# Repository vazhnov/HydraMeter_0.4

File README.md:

# HydraMeter_0.4

Open source [multimeter](https://en.wikipedia.org/wiki/Multimeter)

## Intro

I don't have detailed assembly documents yet, and this isn't really well made for easy assembly in any case, it's a proof of concept at the moment.

There are some more details here: https://hackaday.io/project/176607-hydrameter but it's not much. Mainly a few entries down there's a tour
of how the analog stuff works: https://hackaday.io/project/176607-hydrameter/log/223270-schematic-and-operation

## Repository structure

* Directory [MMTR_AFE_00_04_TORELEASE](./MMTR_AFE_00_04_TORELEASE) contains all schematics and board layouts.
* Directory [MMTR_V00_03_Case](./MMTR_V00_03_Case) contains all the CAD, source type is solidedge (they have a free community edition).
* Directory [Code -> HackBoard_V02_10_shbrd_cal](./Code/HackBoard_V02_10_shbrd_cal/) contains the code for the analog frontend.
* Directory [Code -> Display_VP_10_WirelessV2_SC](./Code/Display_VP_10_WirelessV2_SC/) contains code for the display section.

## Notes

I would recommend 24 to 28 AWG stranded wire for connecting to switches, except the mA/uA switch, for which I'd use 20AWG.
The switches should pull inputs to the 74165s to ground, for numbering you'll have to check the code (or adjust it), when assembled I just
wired up all of them then recorded which switch went where, I don't have a list or diagram. On the board these are labeled A-H, one set
is near the middle of the board, the other next to the module connector.

Hardwired connections are: the two ohms jumpers (J7 and J8) are wired to the second pole of the lower-right switch (right from the front),
and the mA/uA switch goes to J5 and J6.

There's a hardwired connection from J30 to J34, which should be made with at least 18AWG wire, as it carries the full current for the 10A range.

## Tweaks

Note that this version of the PCB has some tweaks from the last manufactured version,
these have not been verified to work.

The as-made PCB is under version 0.3,
however, this version requires significant manual rework including:
* pullup resistors for all switches to D3V3
* cutting jumpers to the Module outputs (J96-99, to configure them as inputs), and wiring switches to them
* additional capacitors on D3V3 to D0V, to stabilize the rail when using a radio module
* DNP U5, and bridge pin 3 to pin 4
* DNP: R74, D5, C72, R76, R77, U26, R78, Q20, Q21, R80, R79
* Replace R33 with a ~16K resistor, or two 33K in parallel
* Manually cut the trace going to pin 10 on U12, U13 and U16 (pulling it to D0V), and wire that pin on the chip to D3V3
* U18 has the wrong footprint (SOIC-16 used on the board, the actual chip is a SOIC-14).
* Angle U18 such that only pins 14-9 make contact with the board (so pins 1-7 are above the surface), and solder in place.
* Then manually wire pins 2-7 to the appropriate pads with short wires.
* If using a battery, a protected cell must be used, there is no circuitry onboard to protect from over or under voltage.
* Positive should be soldered to J10, negative to J11.

To charge, two diodes can be placed in series from VBUS on the
PI pico (MCU_VBUS) to battery positive (charging the battery when USB is plugged in). Bypassing one of the diodes with
a 50 or 100 ohm resistor can improve charge time. This however WILL overcharge the battery if proper cell protection
is not in place! This is a terrible hack solution I used to get something working in like an hour. Use a charger IC
or board or something.

## License

This project uses the CERN Open Hardware Licence Version 2 - Strongly Reciprocal.
Any derived works must fall under the same license and must be open source themselves.

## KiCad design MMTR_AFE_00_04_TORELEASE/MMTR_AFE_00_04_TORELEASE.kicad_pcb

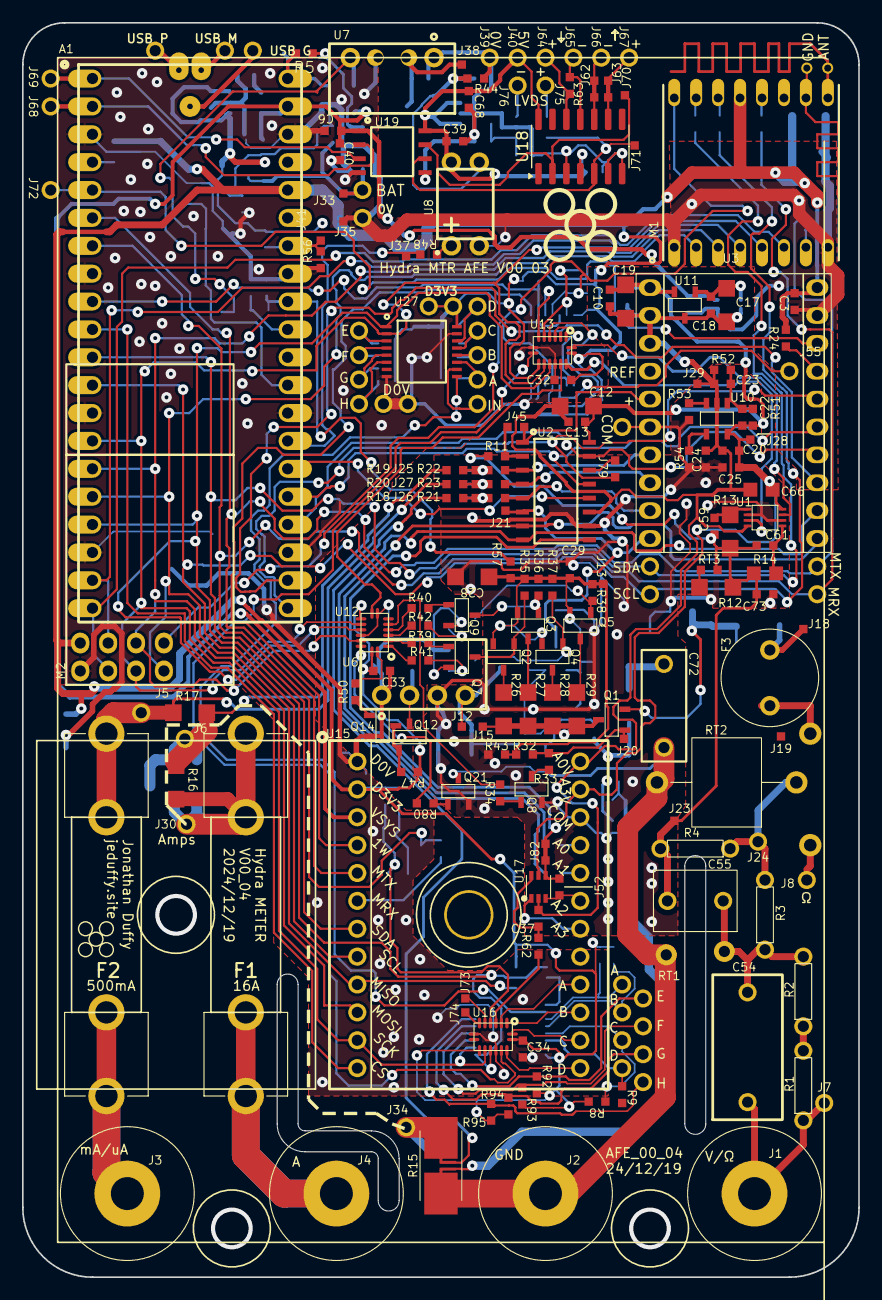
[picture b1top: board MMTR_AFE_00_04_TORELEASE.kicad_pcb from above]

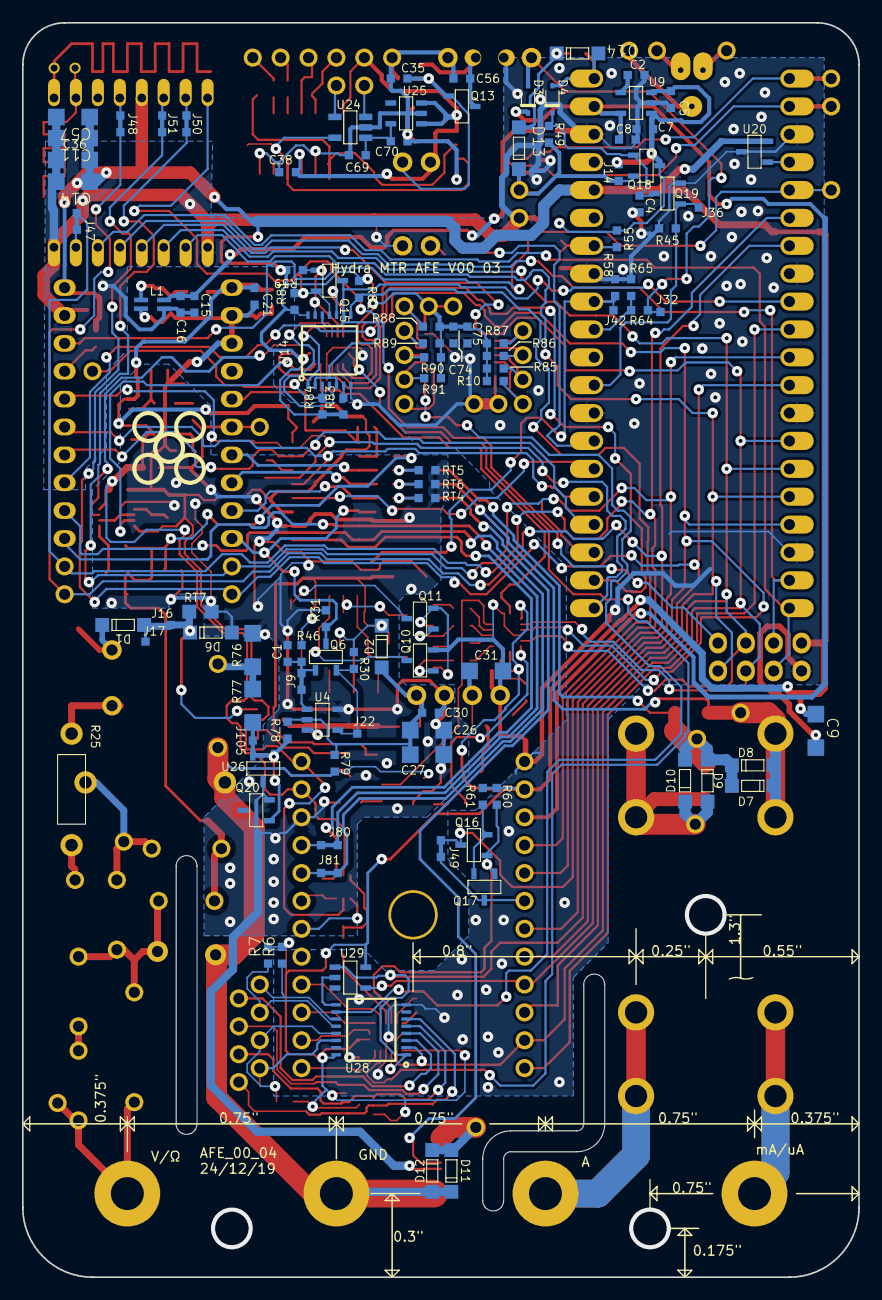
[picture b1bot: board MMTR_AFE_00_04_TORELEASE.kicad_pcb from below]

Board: 2 copper layers, 76.2 x 114.3 mm, 312 parts (109 on the bottom side), 183 nets.

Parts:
A1: Pi Pico; Pi_Pico_WUSB
C1: 10p; Cap_SMD_0603
C2: 100p; Cap_SMD_0603
C3, C5, C6, C13, C16, C18, C20, C22, C23, C29, C30, C32, C33, C34, C35, C37, C38, C39, C40, C69, C74, C75: 100n; Cap_SMD_0603
C4, C21, C56, C68, C70: 1u; Cap_SMD_0603
C7, C8, C15: 2u2; Cap_SMD_0603
C9, C11, C14, C57: 47u; Cap_SMD_1206
C10: 10n; Cap_SMD_0603
C12, C27, C28: 1u; Cap_SMD_1206
C17: 2u2; Cap_SMD_1206
C19, C26, C31, C36: 10u; Cap_SMD_1206
C24, C25: 1n; Cap_SMD_0603
C54: 1.5n; Cap_TH_Film_0.4Spc
C55: 220p; Cap_TH_Film_0.2Spc
C59: 1.8n; Cap_SMD_0603
C61: 27n; Cap_SMD_0603
C66: 100n; Cap_SMD_0805
C72: 0.1u; Cap_TH_Film_0.3Spc
C73: 33p; Cap_SMD_0603
D1, D2, D6, D7, D8, D9, D10, D11, D12, D13, D14: 1N4007FL
D3, D4: CUS08F30,H3F
DM1: Header_Pin_01x01
DP1: Header_Pin_01x01
F1: 16A; FC-102_BRIGHT_TIN
F2: 500mA; FC-102_BRIGHT_TIN
F3: 63mA; 0034.6062
J1, J2, J3, J4: CT2914
J5, J6, J7, J8, J10, J11, J24, J30, J34, J39, J40, J43, J53, J54, J55, J58, J59, J64, J65, J66, J67, J68, J69, J72, J75, J76, J91, J100, J101, J102, J103, J104: Header_Pin_01x01
J9, J47, J48, J49, J50, J51, J62, J63, J80, J81, J82: NC; Jumper_0603
J12, J13, J15, J16, J17, J18, J19, J20, J21, J22, J23, J25, J26, J27, J28, J29, J32, J33, J35, J36, J37, J38, J41, J42, J70, J71, J73, J74, J105: Test_Pad_30x30mil
J14, J45, J52, J79: NO; Jumper_0603_NO
J31: IN_3; Header_Pin_01x01
J44, J46: MiniPin_25mil
J56: IN_2; Header_Pin_01x01
J57: IN_1; Header_Pin_01x01
J60: IN_0; Header_Pin_01x01
J83: IN_8; Header_Pin_01x01
J84: IN_9; Header_Pin_01x01
J85: IN_A; Header_Pin_01x01
J86: IN_B; Header_Pin_01x01
J87: IN_C; Header_Pin_01x01
J88: IN_D; Header_Pin_01x01
J89: IN_E; Header_Pin_01x01
J90: IN_F; Header_Pin_01x01
J92: IN_4; Header_Pin_01x01
J93: IN_5; Header_Pin_01x01
J94: IN_6; Header_Pin_01x01
J95: IN_7; Header_Pin_01x01
L1: 500mOhm; WCM 2012F2SF-361T03
M1: RFM69HCW
M2: NRF24L01
Q1, Q2, Q3, Q4, Q5, Q6, Q12, Q15, Q16, Q17, Q19, Q20: DMN65D8L-7
Q7, Q8, Q9, Q10, Q11, Q13, Q14, Q18, Q21: SOT23-3
R1, R2: 100K; Resistor_THT_Vert_0p2_1o4W
R3, R4: 400K; Resistor_THT_Vert_0p2_1o4W
R5, R54: 50; Resistor_0603
R6, R7, R8, R9, R10, R24, R34, R39, R40, R41, R42, R43, R48, R50, R61, R62, R79, R81, R82, R83, R84, R85, R86, R87, R88, R89, R90, R91, R92, R93, R94, R95: 10K; Resistor_0603
R11, R18, R19, R20, R21, R22, R23, R31, R80: 1K; Resistor_0603
R12: 9M1; Resistor_1206
R13, R28: 100K; Resistor_1206
R14: 6K8; Resistor_0805
R15: 10m; Resistor_2512_4Pin
R16: 330m; Resistor_1206
R17: 100; Resistor_1206
R25: 1K; Resistor_1W_Thru_Wide
R26: 510; Resistor_1206
R27: 10K; Resistor_1206
R29: 1M; Resistor_1206
R30: 3K3; Resistor_0603
R32, R33, R58: 33K; Resistor_0603
R35, R36, R37, R38, R47, R51, R52, R57: 100K; Resistor_0603
R44, R46, R56, R59, R60, R65: 330K; Resistor_0603
R45, R78: 1M; Resistor_0603
R49, R55, R64: 510K; Resistor_0603
R53: 100; Resistor_0603
R63: 120; Resistor_0603
R76: 510K; Resistor_1206
R77: 220K; Resistor_1206
RT1: 230 VRMS; B72205S0231K311
RT2: 75 VRMS; 2045-07-BLF
RT3: 3.3V; MOV_0603
RT4, RT5, RT6: 3V3; MOV_0603
RT7: 18V; MOV_0805
U1: NL7WB66
U2: SOIC-16
U3: 20_Pin_Breakout_0p6_Wd
U4: SOT23-5_LMC7101BYM5-TR
U6: B0309S-1WR3
U7: RFM-0505S
U8: LTV-816
U9: 5V; SOT23-5
U10: SC-74A_LMR312
U11: 3.3V; SOT23-3
U12, U13, U16: 74HC595BQ,115; 16-DHVQFN_74HC595BQ
U14: TC7MBL3126CFT; TSSOP-14_TC7MBL3126CFT
U15: Mmtr_Input_Module
U17: PI5A3157CEX; SC-70_PI5A3157CEX
U18: SP491EEN; SOIC-14_3.9x8.7mm_P1.27mm
U19: STISO621TR; SOIC-8_STISO621TR
U20: 8kbit; SOT23-3
U24: DSLVDS1001DBVR; SC-74A_DSLVDS1001DBVR
U25: 3.3V; SOT23-5
U26: 7Vf 12Vr; SOT23-3
U27, U28: SN74HCS165PWR; TSSOP-16
U29: 74LVC1G126W5-7; SC-74A

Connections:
5V_ISO_IN_EN: A1.27 (GP21), J37.1, R48.2
/Amp_AFE/Amps: F1.1, J4.1
/Amp_AFE/Common_Jack: C72.2, D11.2 (K), D12.1 (A), J2.1, R15.1, RT1.2, RT2.2
/Amp_AFE/mA/uA: F2.1, J3.1
/MCU/0V_ISOLATED: C35.2, C38.2, C39.2, C56.2, C68.2, C69.2, C70.2, J39.1, R44.2, U7.1 (GND), U18.3 (RE), U18.6 (GND), U18.7 (GND), U19.5 (GND2), U24.2 (GND), U25.2 (GND)
/MCU/1Wire: A1.9 (GP6), Q15.3 (D), U14.2 (A1), U14.5 (A2), U14.9 (A3), U14.12 (A4)
/MCU/1Wire0: J55.1, R84.2, U14.3 (B1)
/MCU/1Wire1: R83.2, U14.6 (B2)
/MCU/1Wire_2: R82.2, U14.8 (B3), U15.4 (1Wire)
/MCU/1Wire_3: M1.16 (DIO2), M2.5 (IRQ), Q15.2 (S), R81.2, U14.11 (B4)
/MCU/5V_ISOLATED: C38.1, C39.1, C68.1, J40.1, Q13.2 (S), U8.4 (C), U18.4 (DE), U18.14 (VCC), U19.8 (VDD2), U25.1 (VIN), U25.3 (EN)
/MCU/ADC1: A1.32 (ADC1_GP27), J42.1, R57.1, R58.2
/MCU/CS0: A1.22 (SPI0_CS_GP17), U3.13 (~CS)
/MCU/CS1: A1.26 (GP20), U2.12 (CS)
/MCU/CS_InMod: A1.10 (GP7), U15.12 (CS)
/MCU/GP3: A1.5 (GP3), J72.1, U3.18 (MCLK)
/MCU/IN4: J92.1, R95.1, U28.6 (H)
/MCU/IN5: J93.1, R94.1, U28.5 (G)
/MCU/IN6: J94.1, R93.1, U28.4 (F)
/MCU/IN7: J95.1, R92.1, U28.3 (E)
/MCU/IN8: J83.1, R91.1, U27.11 (A)
/MCU/IN9: J84.1, R90.1, U27.12 (B)
/MCU/IN10: J85.1, R89.1, U27.13 (C)
/MCU/IN11: J86.1, R88.1, U27.14 (D)
/MCU/IN12: J87.1, R87.1, U27.3 (E)
/MCU/IN13: J88.1, R86.1, U27.4 (F)
/MCU/IN14: J89.1, R85.1, U27.5 (G)
/MCU/IN15: J90.1, R10.1, U27.6 (H)
/MCU/MISO: A1.21 (SPI0_MISO_GP16), J79.2, U3.16 (MISO)
/MCU/MOD_ADC0_RAW: J80.1, U15.21 (ADC0)
/MCU/MOD_ADC1_RAW: J81.1, U15.20 (ADC1)
/MCU/MOD_ADC2_RAW: J52.1, U15.19 (ADC2), U17.3 (B0)
/MCU/MOD_ADC3_RAW: U15.18 (ADC3), U17.1 (B1)
/MCU/MOSI: A1.25 (SPI0_MOSI_GP19), U2.13 (MOSI), U3.15 (MOSI)
/MCU/Radio_CS: A1.19 (GP14), M1.5 (NSS), M2.7 (CSN)
/MCU/Radio_DO0: A1.20 (GP15), M1.6 (RESET), M2.2 (CE)
/MCU/SCK: A1.24 (SPI0_SCK_GP18), U2.15 (SCK), U3.14 (SCK)
/MCU/SCL: A1.12 (GP9), J51.2, J59.1, U15.8 (SCL)
/MCU/SDA: A1.11 (GP8), J50.2, J58.1, U15.7 (SDA)
/MCU/SPI1_MISO: A1.16 (GP12), M1.2 (MISO), M2.4 (MISO), U15.9 (MISO), U29.4 (Y)
/MCU/SPI1_MOSI: A1.15 (GP11), M1.3 (MOSI), M2.6 (MOSI), U12.14 (SI), U15.10 (MOSI)
/MCU/SPI1_SCK: A1.14 (GP10), M1.4 (SCK), M2.3 (SCK), U12.11 (SCK), U13.11 (SCK), U15.11 (SCK), U16.11 (SCK), U27.2 (CLK), U28.2 (CLK)
/MCU/SR_In_Pin_0: J31.1, R6.1, U28.11 (A)
/MCU/SR_In_Pin_1: J56.1, R7.1, U28.12 (B)
/MCU/SR_In_Pin_2: J57.1, R8.1, U28.13 (C)
/MCU/SR_In_Pin_3: J60.1, R9.1, U28.14 (D)
/MCU/SR_Pin_0: R80.2, U12.15 (QA)
/MCU/SR_Pin_1: R50.2, U12.1 (QB)
/MCU/SR_Pin_2: R41.1, U12.2 (QC)
/MCU/SR_Pin_3: R39.1, U12.3 (QD)
/MCU/SR_Pin_4: R42.1, U12.4 (QE)
/MCU/SR_Pin_5: R40.1, U12.5 (QF)
/MCU/SR_Pin_6: R34.1, U12.6 (QG)
/MCU/SR_Pin_8: U1.3 (OE2), U13.15 (QA)
/MCU/SR_Pin_9: U1.7 (OE1), U13.1 (QB)
/MCU/SR_Pin_16: U15.13 (DIO0), U16.15 (QA)
/MCU/SR_Pin_17: U15.14 (DIO1), U16.1 (QB)
/MCU/SR_Pin_18: U15.15 (DIO2), U16.2 (QC)
/MCU/SR_Pin_19: U15.16 (DIO3), U16.3 (QD)
/MCU/SR_Pin_20: R62.2, U16.4 (QE)
/MCU/SR_Pin_21: Q16.1 (G), Q17.1 (G), R60.2, U16.5 (QF)
/MCU/SR_Pin_22: J73.1, U16.6 (QG)
/MCU/SR_Pin_23: J74.1, U16.7 (QH)
/MCU/SR_RCK: A1.17 (GP13), U12.12 (RCK), U13.12 (RCK), U16.12 (RCK), U27.1 (SH/~LD), U28.1 (SH/~LD), U29.1 (OE)
/MCU/U1_MRX: A1.7 (U1RX_GP5), J48.2, J49.1, J54.1, Q16.3 (D)
/MCU/U1_MTX: A1.6 (U1TX_GP4), J47.1, J53.1, U15.5 (Meter_TX)
/Ohm_AFE/9V5_Ohms: C26.1, C27.1, C30.1, D2.1 (A), J12.1, R78.1, R79.1, U4.2 (V+), U6.4 (9V)
/Ohm_AFE/Vpin: C54.1, J1.1, J7.1, R1.1
/PGA_ADC/CH0: J45.1, R11.2, U2.2 (CH0)
/PGA_ADC/CH1: R22.2, U2.3 (CH1), U3.7 (CH2)
/PGA_ADC/CH2: R23.2, U2.4 (CH2), U3.8 (CH3)
/PGA_ADC/CH3: R21.2, U2.5 (CH3), U3.9 (CH4)
/PGA_ADC/CH4: J21.1, Q6.3 (D), R31.1, U2.6 (CH4), U3.10 (CH5)
/PGA_ADC/CH5: J80.2, U2.7 (CH5), U3.11 (RES(CH6))
/PGA_ADC/CH6: J81.2, U2.8 (CH6), U3.12 (RES(CH7))
/PGA_ADC/CH7: J82.2, U2.9 (CH7)
/PGA_ADC/~IRQ: R24.2, U3.17 (~IRQ)
A0V: C10.2, C12.2, C13.2, C17.2, C18.2, C19.2, C20.2, C21.2, C23.2, C24.2, C37.2, C66.2, J29.1, L1.3, R52.1, U1.4 (GND), U2.11 (Vss), U3.2 (AGnd), U3.3 (REFIN-), U10.2 (V-), U11.3 (GND), U15.24 (0V_Clean), U17.2 (GND)
A3V3: C10.1, C12.1, C13.1, C19.1, C20.1, C21.1, C22.1, C25.1, C66.1, J28.1, R51.2, U1.8 (VCC), U2.16 (Vdd), U3.1 (AVdd), U10.5 (V+), U11.2 (Vout), U15.23 (3V3_Clean), U17.5 (VDD)
Battery_EN: A1.29 (GP22), J36.1, Q19.1 (G), R45.1
COM: C1.2, C24.1, C25.2, C26.2, C27.2, C28.2, C29.2, C30.2, C73.2, D6.1 (A), J43.1, Q8.2 (E), Q20.2 (S), Q21.2 (E), R12.2, R15.3, R31.2, R43.1, R53.2, R54.2, R76.2, RT3.2, RT4.2, RT5.2, RT6.2, RT7.2, U1.2 (COM1), U1.6 (COM2), U2.10 (Vref), U3.6 (CH1), U4.5 (V-), U6.3 (0V), U15.22 (Common), U26.3 (GND)
D0V: A1.3 (GND), A1.8 (GND), A1.13 (GND), A1.18 (GND), A1.23 (GND), A1.28 (GND), A1.33 (AGND), A1.38 (GND), C2.2, C3.2, C4.2, C5.2, C6.2, C7.2, C8.2, C9.2, C11.2, C14.2, C15.2, C16.2, C31.2, C32.2, C33.2, C34.2, C36.2, C40.2, C57.2, C74.2, C75.2, J11.1, J35.1, J100.1, J101.1, L1.4, M1.1 (GND), M1.8 (GND), M2.1 (GND), Q7.2 (E), Q9.2 (E), Q10.2 (E), Q11.2 (E), Q14.2 (E), Q19.2 (S), R45.2, R56.1, R58.1, R65.1, U3.19 (DGnd), U6.1 (GND), U7.3 (0Vo), U8.2 (K), U9.2 (GND), U12.8 (GND), U12.13 (~G), U13.8 (GND), U13.13 (~G), U14.7 (GND), U15.1 (0V_Dirty), U16.8 (GND), U16.13 (~G), U19.4 (GND1), U20.3 (VSS), U27.8 (GND), U27.15 (CLK_INH), U28.8 (GND), U28.15 (CLK_INH), U29.3 (GND)
D3V3: A1.36 (3V3_OUT), C3.1, C9.1, C11.1, C14.1, C32.1, C33.1, C34.1, C36.1, C57.1, C74.1, C75.1, J102.1, J103.1, M1.13 (3V3), M2.8 (VCC), Q12.2 (S), R6.2, R7.2, R8.2, R9.2, R10.2, R24.1, R47.1, R59.2, R60.1, R61.1, R81.1, R82.1, R83.1, R84.1, R85.2, R86.2, R87.2, R88.2, R89.2, R90.2, R91.2, R92.2, R93.2, R94.2, R95.2, U3.20 (DVdd), U12.10 (~SCLR), U12.16 (VCC), U13.10 (~SCLR), U13.16 (VCC), U14.14 (V+), U15.2 (3V3_Dirty), U16.10 (~SCLR), U16.16 (VCC), U20.2 (VCC), U27.16 (VCC), U28.16 (VCC), U29.5 (Vcc)
MCU_VBUS: A1.40 (VBUS), D4.1 (A), D14.1 (A), R5.1
unnamed: A1.31 (ADC0_GP26), R64.1, R65.2
unnamed: A1.34 (ADC2_GP28), J41.1, R55.1, R56.2
unnamed: A1.42 (DM), DM1.1
unnamed: A1.43 (DP), DP1.1
unnamed: A1.4 (GP2), U20.1 (SCIO)
unnamed: A1.41 (USB_GND), J104.1
unnamed: C54.2, C55.1, R2.2, R3.1, RT1.1
unnamed: C55.2, C59.1, C61.1, C73.1, J23.1, R4.2, R11.1, R12.1, R13.1, R14.1, RT3.1
unnamed: C72.1, R76.1, R77.2
unnamed: D1.1 (A), D6.2 (K), J16.1, J17.1, Q1.2 (S), RT7.1
unnamed: D1.2 (K), F3.2, J18.1
unnamed: C28.1, C29.1, D2.2 (K), J13.1, Q2.2 (S), Q3.2 (S), Q4.2 (S), Q5.2 (S), R30.1, R32.1, R35.1, R36.1, R37.1, R38.1, R43.2, R46.1, R57.2
unnamed: D3.1 (A), J32.1, R64.2, U7.4 (5Vo)
unnamed: C4.1, D4.2 (K), Q18.1 (G), Q19.3 (D), R49.1
unnamed: D7.1 (A), D8.2 (K), F2.2, J5.1, R17.1, R20.1
unnamed: D9.2 (K), D10.1 (A), F1.2, J30.1, R16.2
unnamed: D7.2 (K), D8.1 (A), D9.1 (A), D10.2 (K), J6.1, R16.1, R17.2, R19.1
unnamed: D11.1 (A), D12.2 (K), J34.1, R15.2
unnamed: D13.1 (A), D14.2 (K), R5.2
unnamed: D13.2 (K), J10.1, J14.2, J33.1, Q18.2 (S), R49.2
unnamed: F3.1, J19.1, R25.2
unnamed: J8.1, R25.1
unnamed: J24.1, R3.2, R4.1, RT2.1
unnamed: J25.1, R19.2, R22.1, RT5.1
unnamed: J26.1, R18.2, R21.1, RT4.1
unnamed: J27.1, R20.2, R23.1, RT6.1
unnamed: J46.1, M1.10 (GND)
unnamed: J62.2, J66.1
unnamed: J63.2, J67.1
unnamed: J44.1, M1.9 (ANT)
unnamed: J51.1, M1.14 (DIO0)
unnamed: J50.1, M1.15 (DIO1)
unnamed: J48.1, M1.12 (DIO4)
unnamed: J47.2, M1.7 (DIO5)
unnamed: J15.1, Q1.3 (D), R26.2, R27.2, R28.2, R29.2, U4.3 (IN+)
unnamed: J20.1, Q1.1 (G), R32.2, R33.1
unnamed: Q2.3 (D), R26.1
unnamed: Q2.1 (G), Q7.3 (C), R35.2
unnamed: Q3.3 (D), R27.1
unnamed: Q3.1 (G), Q9.3 (C), R36.2
unnamed: Q4.3 (D), R28.1
unnamed: Q5.3 (D), R29.1
unnamed: C1.1, J9.2, Q6.1 (G), R46.2
unnamed: J22.1, Q6.2 (S), R30.2, U4.4 (IN-)
unnamed: Q7.1 (B), R39.2
unnamed: Q8.1 (B), R34.2
unnamed: Q8.3 (C), R33.2
unnamed: Q9.1 (B), R40.2
unnamed: Q10.1 (B), R41.2
unnamed: Q4.1 (G), Q10.3 (C), R37.2
unnamed: Q11.1 (B), R42.2
unnamed: Q5.1 (G), Q11.3 (C), R38.2
unnamed: C31.1, Q12.3 (D), U6.2 (3V3)
unnamed: Q12.1 (G), Q14.3 (C), R47.2
unnamed: C56.1, J38.1, Q13.3 (D), U7.2 (5Vin)
unnamed: C35.1, Q13.1 (G), R44.1, U8.3 (E)
unnamed: Q14.1 (B), R50.1
unnamed: Q15.1 (G), R59.1, U13.6 (QG), U14.13 (4OE)
unnamed: Q16.2 (S), Q17.2 (S), R61.2
unnamed: J49.2, Q17.3 (D), U15.6 (Meter_RX)
unnamed: J105.1, Q20.1 (G), R77.1, R78.2, U26.1 (IO1), U26.2 (IO2)
unnamed: Q21.1 (B), R80.1
unnamed: Q21.3 (C), R79.2
unnamed: R1.2, R2.1
unnamed: R15.4, R18.1
unnamed: C59.2, R13.2, U1.1 (NO1)
unnamed: C61.2, R14.2, U1.5 (NO2)
unnamed: J45.2, U2.1 (Vout), U3.5 (CH0)
unnamed: J79.1, U2.14 (MISO)
unnamed: J9.1, U4.1 (OUT)
unnamed: R48.1, U8.1 (A)
unnamed: C2.1, U9.4 (BYP)
unnamed: C22.2, C23.1, R51.1, R52.2, U10.1 (IN+)
unnamed: R53.1, U10.3 (IN-)
unnamed: R54.1, U10.4 (OUT)
unnamed: C17.1, C18.1, L1.2, U11.1 (Vin)
unnamed: U12.9 (~QH), U13.14 (SI)
unnamed: U13.4 (QE), U14.1 (OE1)
unnamed: U13.5 (QF), U14.4 (2OE)
unnamed: U13.7 (QH), U14.10 (3OE)
unnamed: U13.9 (~QH), U16.14 (SI)
unnamed: J52.2, J82.1, U17.4 (A)
unnamed: C37.1, R62.1, U17.6 (S)
unnamed: J64.1, R63.1, U18.12 (A)
unnamed: J65.1, R63.2, U18.11 (B)
unnamed: J71.1, U18.5 (D), U19.6 (RX2), U24.5 (TTL_IN)
unnamed: J70.1, U18.2 (R), U19.7 (TX2)
unnamed: J63.1, U18.9 (Y)
unnamed: J62.1, U18.10 (Z)
unnamed: J75.1, U24.4 (OUT+)
unnamed: J76.1, U24.3 (OUT-)
unnamed: C69.1, C70.1, U24.1 (VDD), U25.5 (VOUT)
unnamed: U27.9 (Qh), U28.10 (SER_IN)
unnamed: J91.1, U27.10 (SER_IN)
unnamed: U28.9 (Qh), U29.2 (A)
U0_RX: A1.2 (U0RX_GP1), J68.1, U19.2 (RX1)
U0_TX: A1.1 (U0TX_GP0), J69.1, U19.3 (TX1)
VSYS: A1.39 (VSYS), C6.1, C8.1, C15.1, C16.1, C40.1, D3.2 (K), L1.1, U9.5 (VOUT), U15.3 (5V_Dirty), U19.1 (VDD1)
Vbat: C5.1, C7.1, J14.1, Q18.3 (D), R55.2, U9.1 (Vin), U9.3 (EN)

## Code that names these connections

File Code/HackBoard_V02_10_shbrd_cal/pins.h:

#ifndef PINS_H
#define PINS_H

#define ADC_CS 17
#define PGA_CS 20
#define ADC_MCLK 3

#define SR_RCK 13
#define SPI1_SCK 10
#define SPI1_MOSI 11
#define SPI1_MISO 12
#define RADIO_CS 14
#define RADIO_DO0 15
#define INMOD_CS 7
#define ONEWIRE 6
#define ONEWIRE_BRD 2

#define SDA_PIN 8
#define SCL_PIN 9

#define U0TX 0
#define U0RX 1
#define MTX 4
#define MRX 5

#define BATTERY_EN 22
#define D5V_ISO_EN 21

#define D5V_ISO_SENSE_ANIN 26
#define D5V_ISO_SENSE_CAL (((double)840)/330)
#define HV_SENSE_ANIN 27
#define HV_SENSE_ANIN_CAL (((double)133)/33)
#define VBAT_SENSE_ANIN 28 
#define VBAT_SENSE_ANIN_CAL (((double)840)/330)

#define ATTEN_147_SRPIN 8
#define ATTEN_11_SRPIN 9

#define OHM_PATH_DIS_SRPIN 0
#define OHM_BOOST_EN_SRPIN 1
#define OHMS_510_SRPIN 3
#define OHMS_10K_SRPIN 5
#define OHMS_100K_SRPIN 2
#define OHMS_1M_SRPIN 4
#define OHMS_LOWV_EN_SRPIN 6
#define OHMS_ELOWV_EN_SRPIN 19

#define MODULE_IN23SW_SRPIN 20

#define SWITCH_SRPIN_OHMS     0x0008
#define SWITCH_SRPIN_MA       0x0080

#define SWITCH_SRPIN_SW0      0x4000
#define SWITCH_SRPIN_SW1_UP   0x0800
#define SWITCH_SRPIN_SW1_DN   0x1000
#define SWITCH_SRPIN_SW2_UP   0x0200
#define SWITCH_SRPIN_SW2_DN   0x0400
#define SWITCH_SRPIN_SW3_UP   0x0010
#define SWITCH_SRPIN_SW3_DN   0x0100
#define SWITCH_SRPIN_SW4_UP   0x0040
#define SWITCH_SRPIN_SW4_DN   0x0020
#define SWITCH_SRPIN_SW6_UP   0x0001
#define SWITCH_SRPIN_SW6_DN   0x2000
#define SWITCH_SRPIN_SW7      0x0002
#define SWITCH_SRPIN_SW8      0x0004
#endif

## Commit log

2024-12-11 Initializing repository
    License and readme created
2024-12-21 Initial Commit
    First commit, moving all the current project files to Github
2024-12-25 README.md: remove extra spaces, split to chapters and lists, add headers, move licensing information to the bottom
    No changes in the text itself, only formatting changes.
